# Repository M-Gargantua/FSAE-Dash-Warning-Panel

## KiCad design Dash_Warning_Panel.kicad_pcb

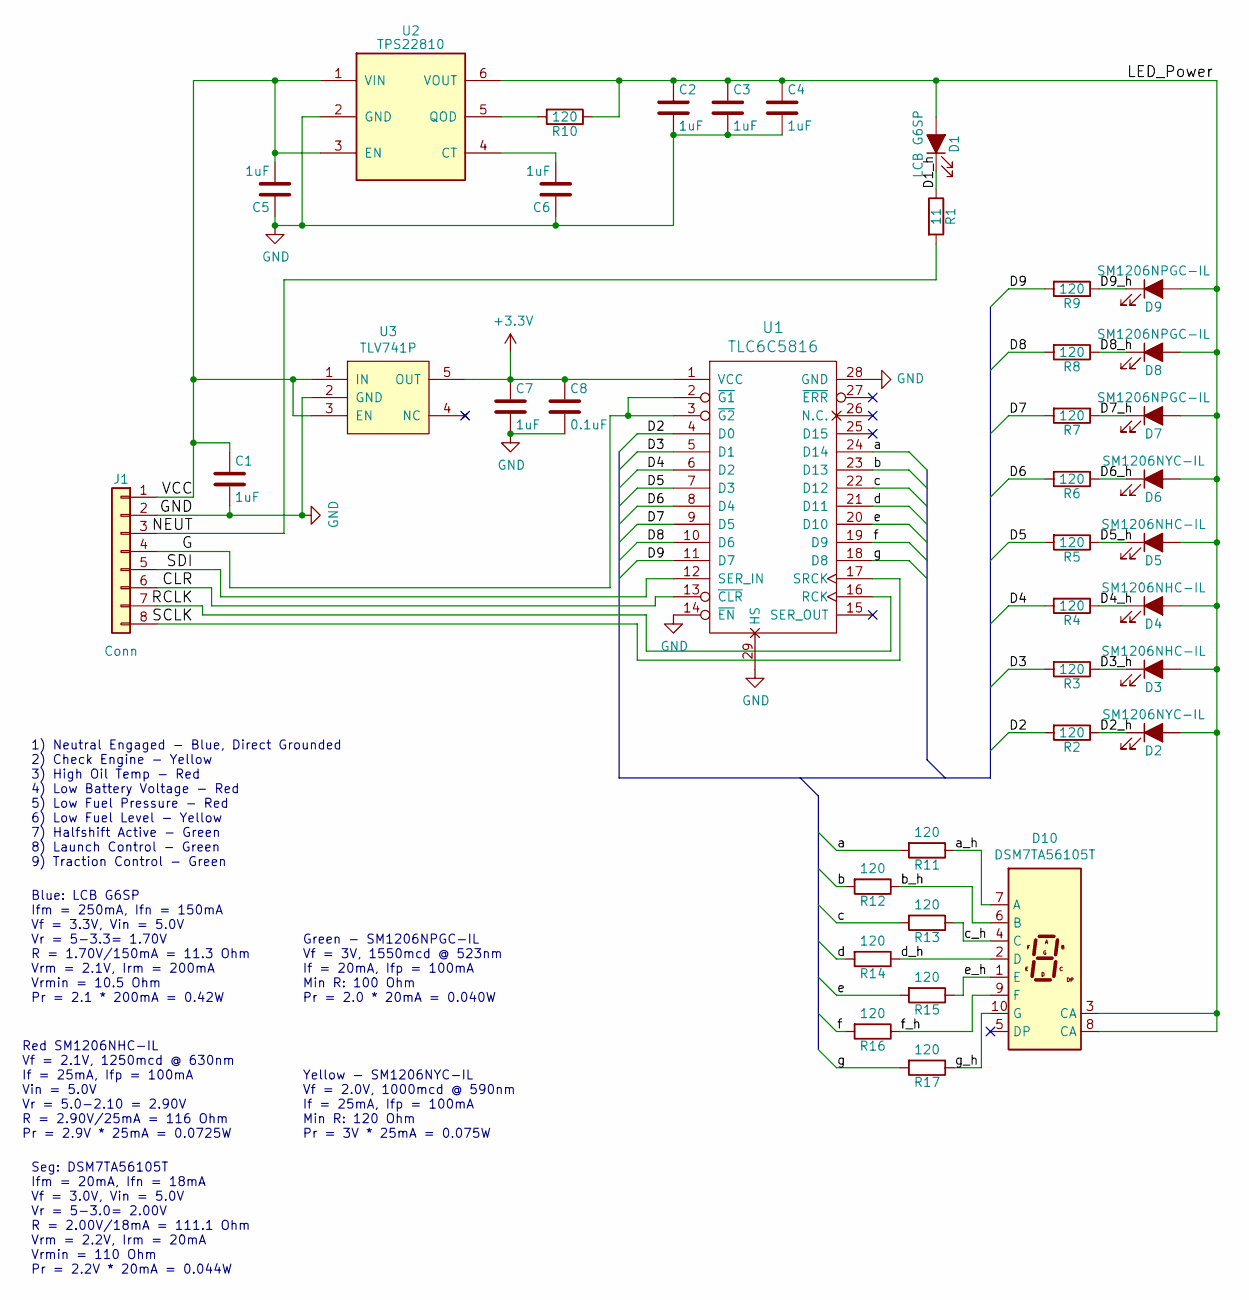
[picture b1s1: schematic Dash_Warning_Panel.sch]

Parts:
C1, C2, C3, C4, C5, C6, C7: 1uF; C_0603; Digikey P/N 399-7847-1-ND
C8: 0.1uF; C_0603; Digikey P/N 399-1099-1-ND
D1: LCB G6SP; PLCC-6_THERM_MOD; Digikey P/N 475-3674-1-ND
D2, D6: SM1206NYC-IL; LED_1206; Digikey P/N 492-1947-1-ND
D3, D4, D5: SM1206NHC-IL; LED_1206; Digikey P/N 492-1944-1-ND
D7, D8, D9: SM1206NPGC-IL; LED_1206; Digikey P/N 492-1945-1-ND
D10: DSM7TA56105T; DSM77TA56105T; Digikey P/N DSM7TA56105TCT-ND
J1: Conn; 8wireConn; Digikey P/N N/A
R1: 11; R_1210; Digikey P/N 541-11.0AACT-ND
R2, R3, R4, R5, R6, R7, R8, R9, R10, R11, R12, R13, R14, R15, R16, R17: 120; R_0603; Digikey P/N RMCF0603FT120RCT-ND
U1: TLC6C5816; HTSSOP-28_4.4x9.7mm_Pitch0.65mm_ThermalPad; Digikey P/N 296-51674-1-ND
U2: TPS22810; SOT-23-6; Digikey P/N 296-45297-1-ND
U3: TLV741P; SOT-23-5; Digikey P/N 296-48987-1-ND

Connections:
+3V3: C7.1, C8.1, U1.1 (VCC), U3.5 (OUT)
/CLR: J1.6, U1.13 (~CLR)
/D1_h: D1.1 (K), R1.1
/D2: R2.2, U1.4 (D0)
/D2_h: D2.1 (K), R2.1
/D3: R3.2, U1.5 (D1)
/D3_h: D3.1 (K), R3.1
/D4: R4.2, U1.6 (D2)
/D4_h: D4.1 (K), R4.1
/D5: R5.2, U1.7 (D3)
/D5_h: D5.1 (K), R5.1
/D6: R6.2, U1.8 (D4)
/D6_h: D6.1 (K), R6.1
/D7: R7.2, U1.9 (D5)
/D7_h: D7.1 (K), R7.1
/D8: R8.2, U1.10 (D6)
/D8_h: D8.1 (K), R8.1
/D9: R9.2, U1.11 (D7)
/D9_h: D9.1 (K), R9.1
/G: J1.4, U1.2 (~G1), U1.3 (~G2)
/LED_Power: C2.1, C3.1, C4.1, D1.2 (A), D2.2 (A), D3.2 (A), D4.2 (A), D5.2 (A), D6.2 (A), D7.2 (A), D8.2 (A), D9.2 (A), D10.3 (CA), D10.8 (CA), R10.1, U2.6 (VOUT)
/NEUT: J1.3, R1.2
/RCLK: J1.7, U1.16 (RCK)
/SCLK: J1.8, U1.17 (SRCK)
/SDI: J1.5, U1.12 (SER_IN)
/VCC: C1.1, C5.2, J1.1, U2.1 (VIN), U2.3 (EN), U3.1 (IN), U3.3 (EN)
/a: R11.2, U1.24 (D14)
/a_h: D10.7 (A), R11.1
/b: R12.2, U1.23 (D13)
/b_h: D10.6 (B), R12.1
/c: R13.2, U1.22 (D12)
/c_h: D10.4 (C), R13.1
/d: R14.2, U1.21 (D11)
/d_h: D10.2 (D), R14.1
/e: R15.2, U1.20 (D10)
/e_h: D10.1 (E), R15.1
/f: R16.2, U1.19 (D9)
/f_h: D10.9 (F), R16.1
/g: R17.2, U1.18 (D8)
/g_h: D10.10 (G), R17.1
GND: C1.2, C2.2, C3.2, C4.2, C5.1, C6.1, C7.2, C8.2, J1.2, U1.14 (~EN), U1.28 (GND), U1.29 (HS), U2.2 (GND), U3.2 (GND)
unnamed: C6.2, U2.4 (CT)
unnamed: R10.2, U2.5 (QOD)

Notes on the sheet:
Yellow - SM1206NYC-IL Vf = 2.0V, 1000mcd @ 590nm If = 25mA, Ifp = 100mA Min R: 120 Ohm Pr = 3V * 25mA = 0.075W
Red SM1206NHC-IL Vf = 2.1V, 1250mcd @ 630nm If = 25mA, Ifp = 100mA Vin = 5.0V Vr = 5.0-2.10 = 2.90V R = 2.90V/25mA = 116 Ohm Pr = 2.9V * 25mA = 0.0725W
Green - SM1206NPGC-IL Vf = 3V, 1550mcd @ 523nm If = 20mA, Ifp = 100mA Min R: 100 Ohm Pr = 2.0 * 20mA = 0.040W
1) Neutral Engaged - Blue, Direct Grounded 2) Check Engine - Yellow 3) High Oil Temp - Red 4) Low Battery Voltage - Red 5) Low Fuel Pressure - Red 6) Low Fuel Level - Yellow 7) Halfshift Active - Green 8) Launch Control - Green 9) Traction Control - Green
Blue: LCB G6SP Ifm = 250mA, Ifn = 150mA Vf = 3.3V, Vin = 5.0V Vr = 5-3.3= 1.70V R = 1.70V/150mA = 11.3 Ohm Vrm = 2.1V, Irm = 200mA Vrmin = 10.5 Ohm Pr = 2.1 * 200mA = 0.42W
Seg: DSM7TA56105T Ifm = 20mA, Ifn = 18mA Vf = 3.0V, Vin = 5.0V Vr = 5-3.0= 2.00V R = 2.00V/18mA = 111.1 Ohm Vrm = 2.2V, Irm = 20mA Vrmin = 110 Ohm Pr = 2.2V * 20mA = 0.044W

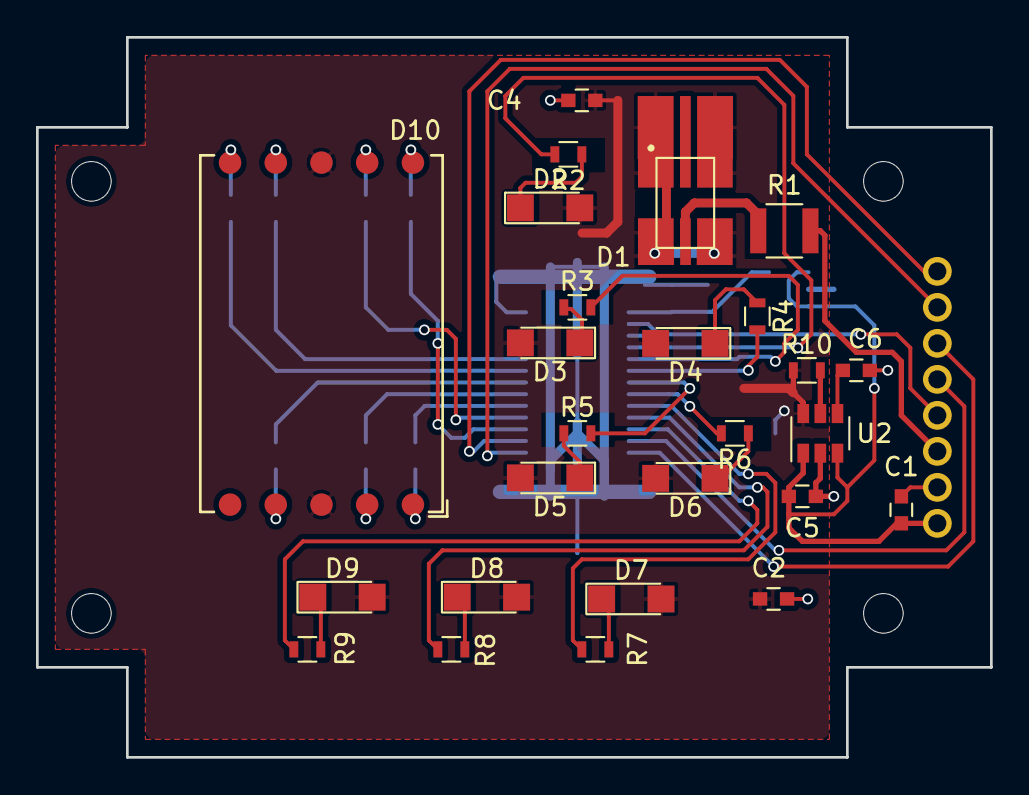
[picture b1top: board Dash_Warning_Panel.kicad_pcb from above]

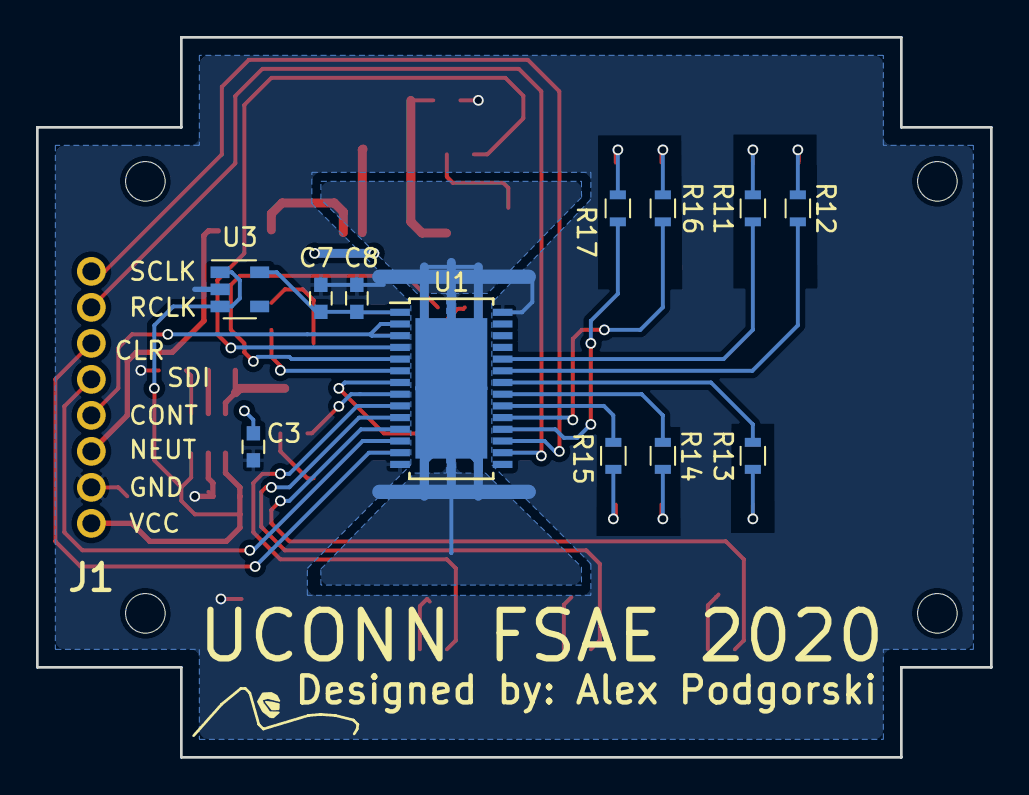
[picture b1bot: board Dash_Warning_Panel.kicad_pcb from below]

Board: 2 copper layers, 53.0 x 40.0 mm, 39 parts (13 on the bottom side), 43 nets.

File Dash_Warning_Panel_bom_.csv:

Component,Description,Part,References,Value,Footprint,Quantity Per PCB,Datasheet,P/N,MFG,Sheetpath,Digikey P/N
1,Unpolarized capacitor,C,C8,0.1uF,C_0603,1,https://api.kemet.com/component-edge/download/datasheet/C060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,C0603C104M4RACTU,KEMET,/,399-1099-1-ND
2,Unpolarized capacitor,C,C1 C2 C3 C4 C5 C6 C7,1uF,C_0603,7,,C0603C105K4RACTU,KEMET,/,399-7847-1-ND
3,"VCC One digit 7 segment green, common anode",DSM7TA56105T,D10,DSM7TA56105T,DSM77TA56105T,1,https://vcclite.com/wp-content/uploads/wpallimport/files/fil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,DSM7TA56105T,VCC,/,DSM7TA56105TCT-ND
4,"Light emitting diode, filled shape",LED_ALT,D1,LCB G6SP,PLCC-6_THERM_MOD,1,https://dammedia.osram.info/media/resource/hires/osram-dam-6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,LCB G6SP-DBFA-4J5L-0-140-R18-Z,OSRAM,/,475-3674-1-ND
5,"Light emitting diode, filled shape",LED_ALT,D3 D4 D5,SM1206NHC-IL,LED_1206,3,https://www.bivar.com/Portals/0/Products/SM1206NHC-IL.pdf,SM1206NHC-IL,BIVAR,/,492-1944-1-ND
6,"Light emitting diode, filled shape",LED_ALT,D7 D8 D9,SM1206NPGC-IL,LED_1206,3,https://www.bivar.com/parts_content/Datasheets/SM1206NPGC-IL.pdf,SM1206NPGC-IL,BIVAR,/,492-1945-1-ND
7,"Light emitting diode, filled shape",LED_ALT,D2 D6,SM1206NYC-IL,LED_1206,2,https://www.bivar.com/Files/Datasheets/SM1206NYC-IL.pdf,SM1206NYC-IL,BIVAR,/,492-1947-1-ND
8,"Generic connector, single row, 01x08, script generated (kicad-library-utils/schlib/autogen/connector/)",Conn_01x08,J1,Conn,8wireConn,1,N/A,N/A,N/A,/,N/A
9,Resistor,R,R1,11,R_1210,1,http://www.vishay.com/docs/20035/dcrcwe3.pdf,CRCW121011R0FKEA,Vishay,/,541-11.0AACT-ND
10,Resistor,R,R2 R3 R4 R5 R6 R7 R8 R9 R10 R11 R12 R13 R14 R15 R16 R17,120,R_0603,16,https://www.seielect.com/catalog/sei-rmcf_rmcp.pdf,RMCF0603FT120R,Stackpole,/,RMCF0603FT120RCT-ND
11,16-Bit Line Driver Shift Register with Diagnostics,TLC6C5816,U1,TLC6C5816,HTSSOP-28_4.4x9.7mm_Pitch0.65mm_ThermalPad,1,https://www.ti.com/lit/ds/symlink/tlc6c5816-q1.pdf,TLC6C5816QPWPRQ1,TI,/,296-51674-1-ND
12,TI 150mA 3.3V Fixed LDO linear regulator 1% SOT-23-5,TLV741P,U3,TLV741P,SOT-23-5,1,https://www.ti.com/lit/ds/symlink/tlv741p.pdf,TLV74133PDBVR,TI,/,296-48987-1-ND
13,Single power-distribution switcher,TPS22810-Q1,U2,TPS22810,SOT-23-6,1,https://www.ti.com/lit/ds/symlink/tps22810.pdf,TPS22810DBVR,TI,/,296-45297-1-ND

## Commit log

2018-10-12 Initial Design
    Takes a 6pin FPC connector with +5V, GND, LED 1 Drain, SDO, SDI, and SCLK. Serial goes to a ROHM 24ch RGB LED driver board to control LED 2-9. Includes a power switch to limit inrush current to LED p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
2018-10-12 Fixed Ground Pour and Silkscreen
2018-10-12 Fixed C6 footprint
2018-10-18 Base Production
    Extended Board Outline, Fixed Solder Mask overlay, added ground via's for thermal pad under U1, added flood fill capacitors for VCC and LED Power in unoccupied boardspace.
2019-03-20 Fabrication 2
2019-03-21 Fabrication 2
    Flipped side for switch
2019-03-28 Production 2
2019-04-16 Fixed I2C
    Address is 01111000
2019-04-25 LP5024
2019-04-27 Routing with LP5024
    Ready for Fabrication Review
2020-02-21 2020 Warning Panel Design
    Added Green 7 Segment Display driven by shift driver
    Light 1 changed to Neutral Engage Direct driven diode off 5V power system
    Light 2-9 all off of shift driver
    Standardized LEDs and resistors with main panel
2020-02-23 2020 Initial Design
    2020 Initial Design Submission:
    Connector changed to 8 pin Molex 90 degree KK
    Added Seven Segment Display
2020-06-26 First Manufacture Ready 2020
2020-06-27 Updated BOM and part number data
2020-07-18 Added LDO 3.3V Reg
2021-02-19 Release Candidate 1
    Fixed Blue LED ambiguity
2023-01-30 Backlog Push
    Whatever Changed since 2021
